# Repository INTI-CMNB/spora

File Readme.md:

SPORA PRE-RELEASE
==================

BUILD AWESOME WEARABLES

Open hardware platform for wearables.

Lots of sensors ready to use, program and expand at ease. All packed in an incredible small size.
More info at [Spora web page](https://sporaio.com/).

Final release in [Spora repo](https://github.com/sporaio).

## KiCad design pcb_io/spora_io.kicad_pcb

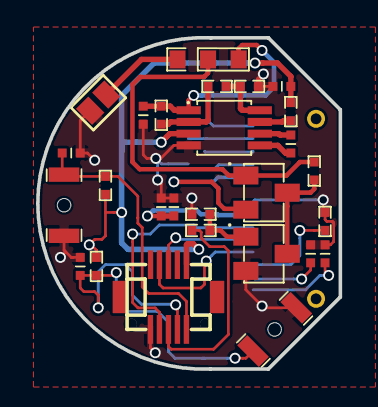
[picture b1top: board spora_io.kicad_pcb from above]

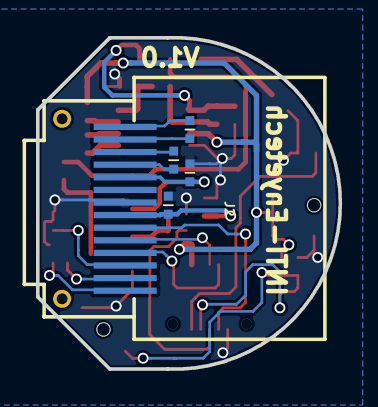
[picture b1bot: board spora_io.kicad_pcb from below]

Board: 2 copper layers, 16.8 x 18.4 mm, 32 parts (5 on the bottom side), 27 nets.

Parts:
C1, C2, C5, C6, C11, C12: 1uF; c_0402
C3: 2.2uF; c_0402
C4: 4.7uF; c_0402
C7, C8: 0.1uF; c_0402
C9, C10: 10 uF; c_0402
C13: 1 uF; c_0402
CON2: VBA_IN; GS2
J1: DF12B 3.0 10DS 0.5V 81; df12(3.0)-10ds-0.5v
J2: ER-OLED0.49-1Series; ER-OLED0.49-1_B
JP1: JUMPER; JUMPER3_0603
Q1: FDN335N_NMOS; SSOT-3
Q2: FDN338P_PMOS; SSOT-3
R1: 390K; r_0402
R2, R3, R7, R9, R10, R11: 10K; r_0402
R6: 23.2 K; r_0402
R12: 0 ohm; r_0402
R13: 100K; r_0402
SW1, SW2: SW_PUSH; B3U_3000PB
U1: MCP1252-ADJ; MSOP-8

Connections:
+3V3: C9.1, J1.1, R2.1, R3.1, R13.1, U1.3
/BOTON_CENTRO: C8.1, J1.10, R3.2, SW2.2
/BOTON_IZQUIERDO: C7.1, J1.9, R2.2, SW1.2
/GPIO_OLED: J1.8, R12.1
/RESET_OLED: J1.7, J2.9
/SCL: J1.3, J2.10
/SDA: J1.4, J2.11
/VBAT: C5.1, J2.5, Q2.2
/VBAT_+: CON2.1, JP1.3
/VBAT_DC_DC: C10.1, JP1.1, R11.1, U1.1
/VBAT_IN: JP1.2, Q2.1, R10.1
/VDD: C6.1, C11.1, C12.1, J2.8
GND: C3.2, C4.2, C5.2, C6.2, C7.2, C8.2, C9.2, C10.2, C11.2, C12.2, CON2.2, J1.6, J2.7, Q1.2, R1.2, R7.2, R9.2, SW1.1, SW2.1, U1.4
unnamed: C1.1, J2.2
unnamed: C1.2, J2.1
unnamed: C2.1, J2.3
unnamed: C2.2, J2.4
unnamed: C3.1, J2.14
unnamed: C4.1, J2.13
unnamed: C13.1, U1.6
unnamed: C13.2, U1.5
unnamed: J2.12, R1.1
unnamed: Q1.1, R9.1, R12.2
unnamed: Q1.3, Q2.3, R10.2
unnamed: R6.2, R7.1, U1.8
unnamed: R6.1, R11.2, U1.2
unnamed: R13.2, U1.7

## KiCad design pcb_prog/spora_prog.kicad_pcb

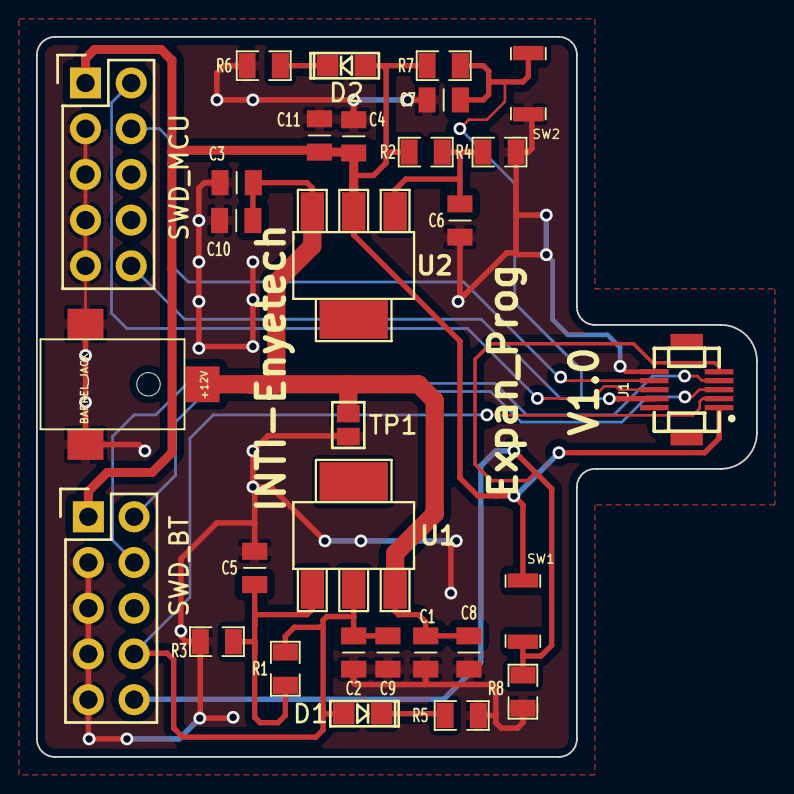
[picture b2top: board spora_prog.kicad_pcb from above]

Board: 2 copper layers, 40.0 x 40.0 mm, 30 parts (0 on the bottom side), 14 nets.

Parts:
+12V: BARREL_JACK; Pj-38-smt
C1, C2, C3, C4, C5, C6: 10uF; c_0805
C7, C8, C9, C10, C11: 0.1uF; c_0805
D1, D2: Led; LED-0805
J1: DF12B-3.0-10DS-0.5V-81; df12(3.0)-10ds-0.5v
R1: 270; r_0805
R2: 470; r_0805
R3: 1,2k; r_0805
R4: 280; r_0805
R5: 10K; r_0805
R6, R7: 4,7K; r_0805
R8: 4K7; r_0805
SW1, SW2: SIDE_SW; B3U_1000PB
SWD_BT: SWD_BT; Pin_Header_Straight_2x05
SWD_MCU: SWD_MCU; Pin_Header_Straight_2x05
TP1: TP1; GS2
U1, U2: LM1117; sot223

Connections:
+3V3: C4.1, C11.1, D2.2, J1.1, R2.1, R7.2, SW1.2, SWD_BT.1, SWD_MCU.1, U2.2
+12V: +12V.1, C1.1, C3.1, C8.1, C10.1, TP1.1, U1.3, U2.3
/RST_BT: J1.5, R8.2, SW1.1, SWD_BT.10
/SWD_CLK_BT: J1.4, SWD_BT.4
/SWD_CLK_MCU: J1.7, SWD_MCU.4
/SWD_DIO_BT: J1.3, SWD_BT.2
/SWD_DIO_MCU: J1.8, SWD_MCU.2
/~RESET_b: C7.1, J1.9, R7.1, SW2.2, SWD_MCU.10
GND: +12V.2, +12V.3, C1.2, C2.2, C3.2, C4.2, C5.2, C6.2, C7.2, C8.2, C9.2, C10.2, C11.2, J1.6, R3.2, R4.2, R5.1, R6.1, R8.1, SW2.1, SWD_BT.3, SWD_BT.5, SWD_BT.7, SWD_BT.9, SWD_MCU.3, SWD_MCU.5, SWD_MCU.7, SWD_MCU.9, TP1.2
unnamed: C5.1, R1.2, R3.1, U1.1
unnamed: C6.1, R2.2, R4.1, U2.1
unnamed: D1.1, R5.2
unnamed: D2.1, R6.2
VPP: C2.1, C9.1, D1.2, J1.2, R1.1, SWD_BT.8, U1.2

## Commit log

2017-07-29 Files from first prototype.
2019-01-16 Link to official repo added.
2019-01-16 Typo.

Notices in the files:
pcb_prog/spora_prog.kicad_pcb:
BSD License. See LICENSE.txt
